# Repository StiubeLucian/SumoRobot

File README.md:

# SumoRobot
Initial Creation of a complete sumo mega firmware with oled screen and multiple settings available.

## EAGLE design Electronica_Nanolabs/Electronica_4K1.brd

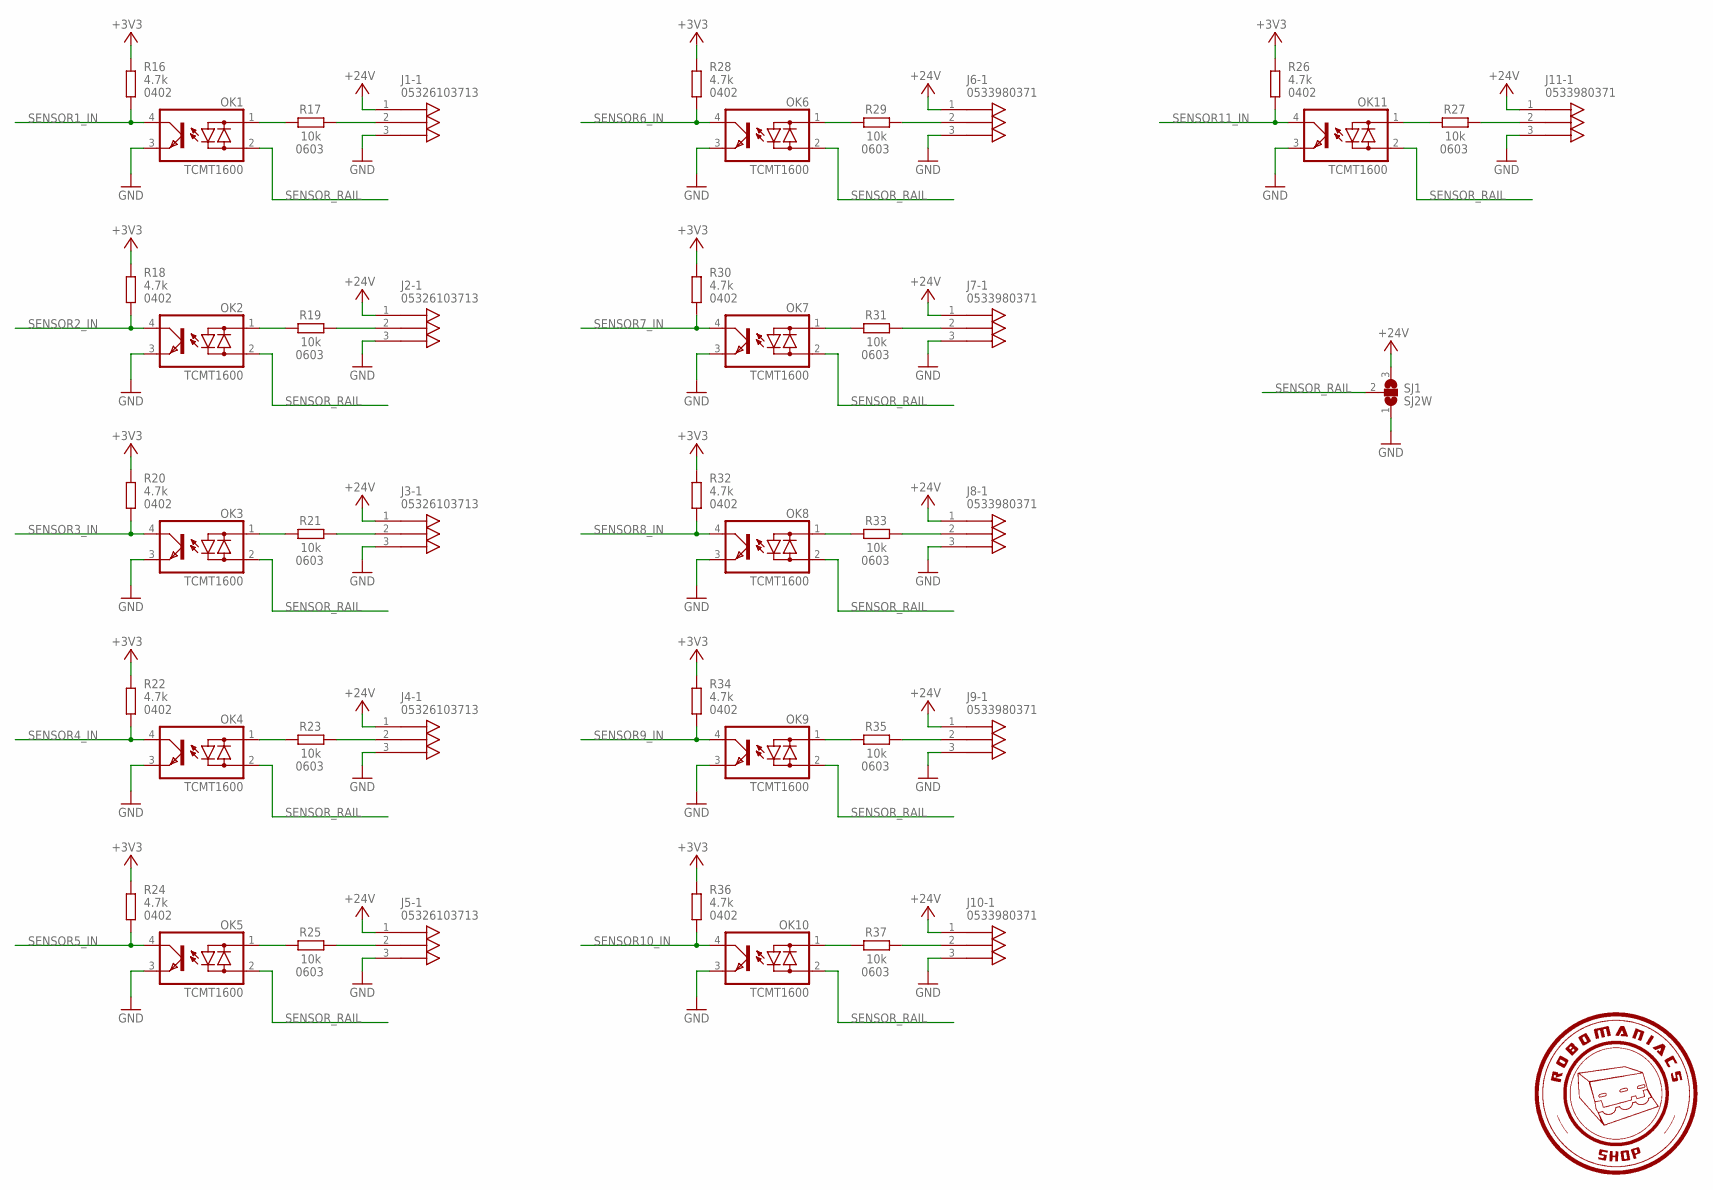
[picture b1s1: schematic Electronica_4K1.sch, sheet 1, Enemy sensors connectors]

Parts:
J1, J2, J3, J4, J5: 05326103713; PICOBLADE53261-0371
J6, J7, J8, J9, J10, J11: 0533980371; PICOBLADE53398-0571
OK1, OK2, OK3, OK4, OK5, OK6, OK7, OK8, OK9, OK10, OK11: TCMT1600; SOP-4
R16, R18, R20, R22, R24, R26, R28, R30, R32, R34, R36: 4.7k; R0402_IPC; MPN AC0402FR-074K7L
R17, R19, R21, R23, R25, R27, R29, R31, R33, R35, R37: 10k; R0603
SJ1: SJ2W; SJ2W_1X1.5_NO

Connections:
+3V3: R16.1, R18.1, R20.1, R22.1, R24.1, R26.1, R28.1, R30.1, R32.1, R34.1, R36.1; also elsewhere on the board
+24V: J1.1, J2.1, J3.1, J4.1, J5.1, J6.1, J7.1, J8.1, J9.1, J10.1, J11.1, SJ1.3; also elsewhere on the board
GND: J1.3, J2.3, J3.3, J4.3, J5.3, J6.3, J7.3, J8.3, J9.3, J10.3, J11.3, OK1.3 (E), OK2.3 (E), OK3.3 (E), OK4.3 (E), OK5.3 (E), OK6.3 (E), OK7.3 (E), OK8.3 (E), OK9.3 (E), OK10.3 (E), OK11.3 (E), SJ1.1; also elsewhere on the board
unnamed: J1.2, R17.2
unnamed: J2.2, R19.2
unnamed: OK1.1 (AC1), R17.1
unnamed: OK2.1 (AC1), R19.1
unnamed: J3.2, R21.2
unnamed: OK3.1 (AC1), R21.1
unnamed: J4.2, R23.2
unnamed: OK4.1 (AC1), R23.1
unnamed: J5.2, R25.2
unnamed: OK5.1 (AC1), R25.1
unnamed: J11.2, R27.2
unnamed: OK11.1 (AC1), R27.1
unnamed: J6.2, R29.2
unnamed: OK6.1 (AC1), R29.1
unnamed: J7.2, R31.2
unnamed: OK7.1 (AC1), R31.1
unnamed: J8.2, R33.2
unnamed: OK8.1 (AC1), R33.1
unnamed: J9.2, R35.2
unnamed: OK9.1 (AC1), R35.1
unnamed: J10.2, R37.2
unnamed: OK10.1 (AC1), R37.1
SENSOR1_IN: OK1.4 (C), R16.2; also elsewhere on the board
SENSOR2_IN: OK2.4 (C), R18.2; also elsewhere on the board
SENSOR3_IN: OK3.4 (C), R20.2; also elsewhere on the board
SENSOR4_IN: OK4.4 (C), R22.2; also elsewhere on the board
SENSOR5_IN: OK5.4 (C), R24.2; also elsewhere on the board
SENSOR6_IN: OK6.4 (C), R28.2; also elsewhere on the board
SENSOR7_IN: OK7.4 (C), R30.2; also elsewhere on the board
SENSOR8_IN: OK8.4 (C), R32.2; also elsewhere on the board
SENSOR9_IN: OK9.4 (C), R34.2; also elsewhere on the board
SENSOR10_IN: OK10.4 (C), R36.2; also elsewhere on the board
SENSOR11_IN: OK11.4 (C), R26.2; also elsewhere on the board
SENSOR_RAIL: OK1.2 (AC2), OK2.2 (AC2), OK3.2 (AC2), OK4.2 (AC2), OK5.2 (AC2), OK6.2 (AC2), OK7.2 (AC2), OK8.2 (AC2), OK9.2 (AC2), OK10.2 (AC2), OK11.2 (AC2), SJ1.2

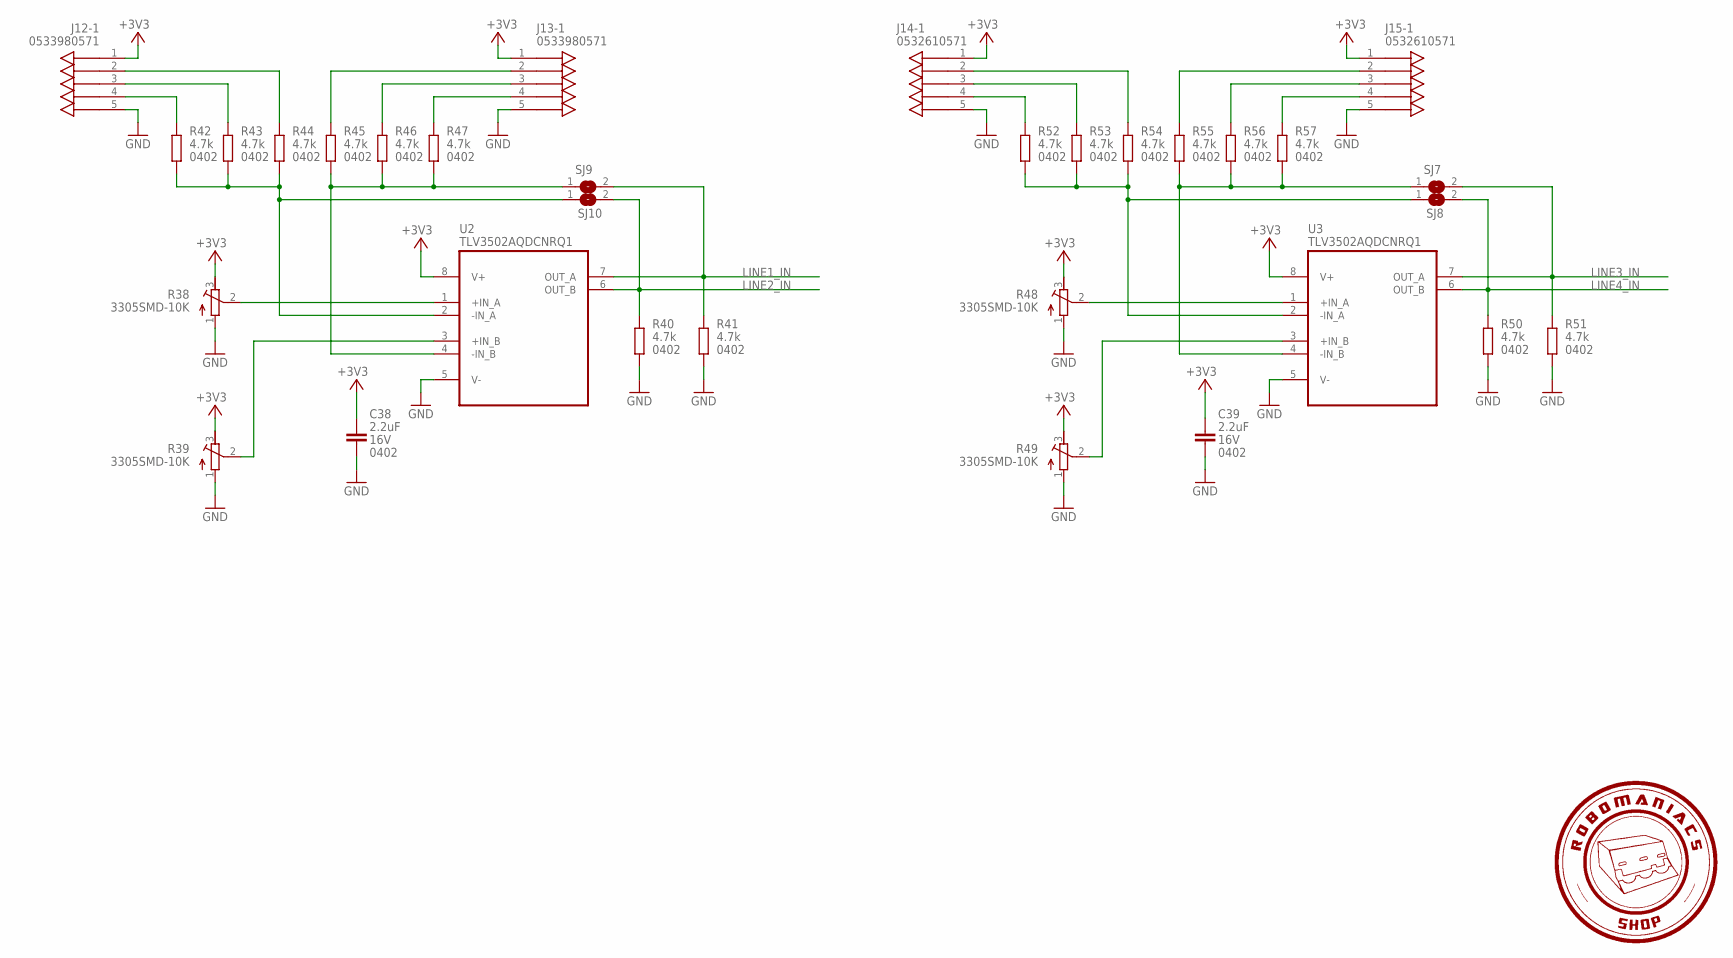
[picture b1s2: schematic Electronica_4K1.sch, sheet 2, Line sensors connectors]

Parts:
C38, C39: 2.2uF; C0402_IPC; VOLTAGE 16V; MPN GRM155R61C225ME15D
J12, J13: 0533980571; PICOBLADE53398-0571
J14, J15: 0532610571; PICOBLADE53261-0571
R38, R39, R48, R49: 3305SMD-10K; RTRIM3103
R40, R41, R42, R43, R44, R45, R46, R47, R50, R51, R52, R53, R54, R55, R56, R57: 4.7k; R0402_IPC; MPN AC0402FR-074K7L
SJ7, SJ8, SJ9, SJ10: SJ_1.5X1_NO; SJ_1X1.5_NO
U2, U3: TLV3502AQDCNRQ1; SOT65P280X145-8N

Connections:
+3V3: C38.1, C39.1, J12.1, J13.1, J14.1, J15.1, R38.3 (E), R39.3 (E), R48.3 (E), R49.3 (E), U2.8 (V+), U3.8 (V+); also elsewhere on the board
GND: C38.2, C39.2, J12.5, J13.5, J14.5, J15.5, R38.1 (A), R39.1 (A), R40.2, R41.2, R48.1 (A), R49.1 (A), R50.2, R51.2, U2.5 (V-), U3.5 (V-); also elsewhere on the board
LINE1_IN: R41.1, SJ9.2, U2.7 (OUT_A); also elsewhere on the board
LINE2_IN: R40.1, SJ10.2, U2.6 (OUT_B); also elsewhere on the board
LINE3_IN: R51.1, SJ7.2, U3.7 (OUT_A); also elsewhere on the board
LINE4_IN: R50.1, SJ8.2, U3.6 (OUT_B); also elsewhere on the board
unnamed: R38.2 (S), U2.1 (+IN_A)
unnamed: R39.2 (S), U2.3 (+IN_B)
unnamed: R42.2, R43.2, R44.2, SJ10.1, U2.2 (-IN_A)
unnamed: R45.2, R46.2, R47.2, SJ9.1, U2.4 (-IN_B)
unnamed: J13.4, R47.1
unnamed: J13.3, R46.1
unnamed: J12.4, R42.1
unnamed: J12.3, R43.1
unnamed: J12.2, R44.1
unnamed: J13.2, R45.1
unnamed: R48.2 (S), U3.1 (+IN_A)
unnamed: R49.2 (S), U3.3 (+IN_B)
unnamed: R52.2, R53.2, R54.2, SJ8.1, U3.2 (-IN_A)
unnamed: R55.2, R56.2, R57.2, SJ7.1, U3.4 (-IN_B)
unnamed: J14.4, R52.1
unnamed: J14.3, R53.1
unnamed: J14.2, R54.1
unnamed: J15.4, R57.1
unnamed: J15.3, R56.1
unnamed: J15.2, R55.1

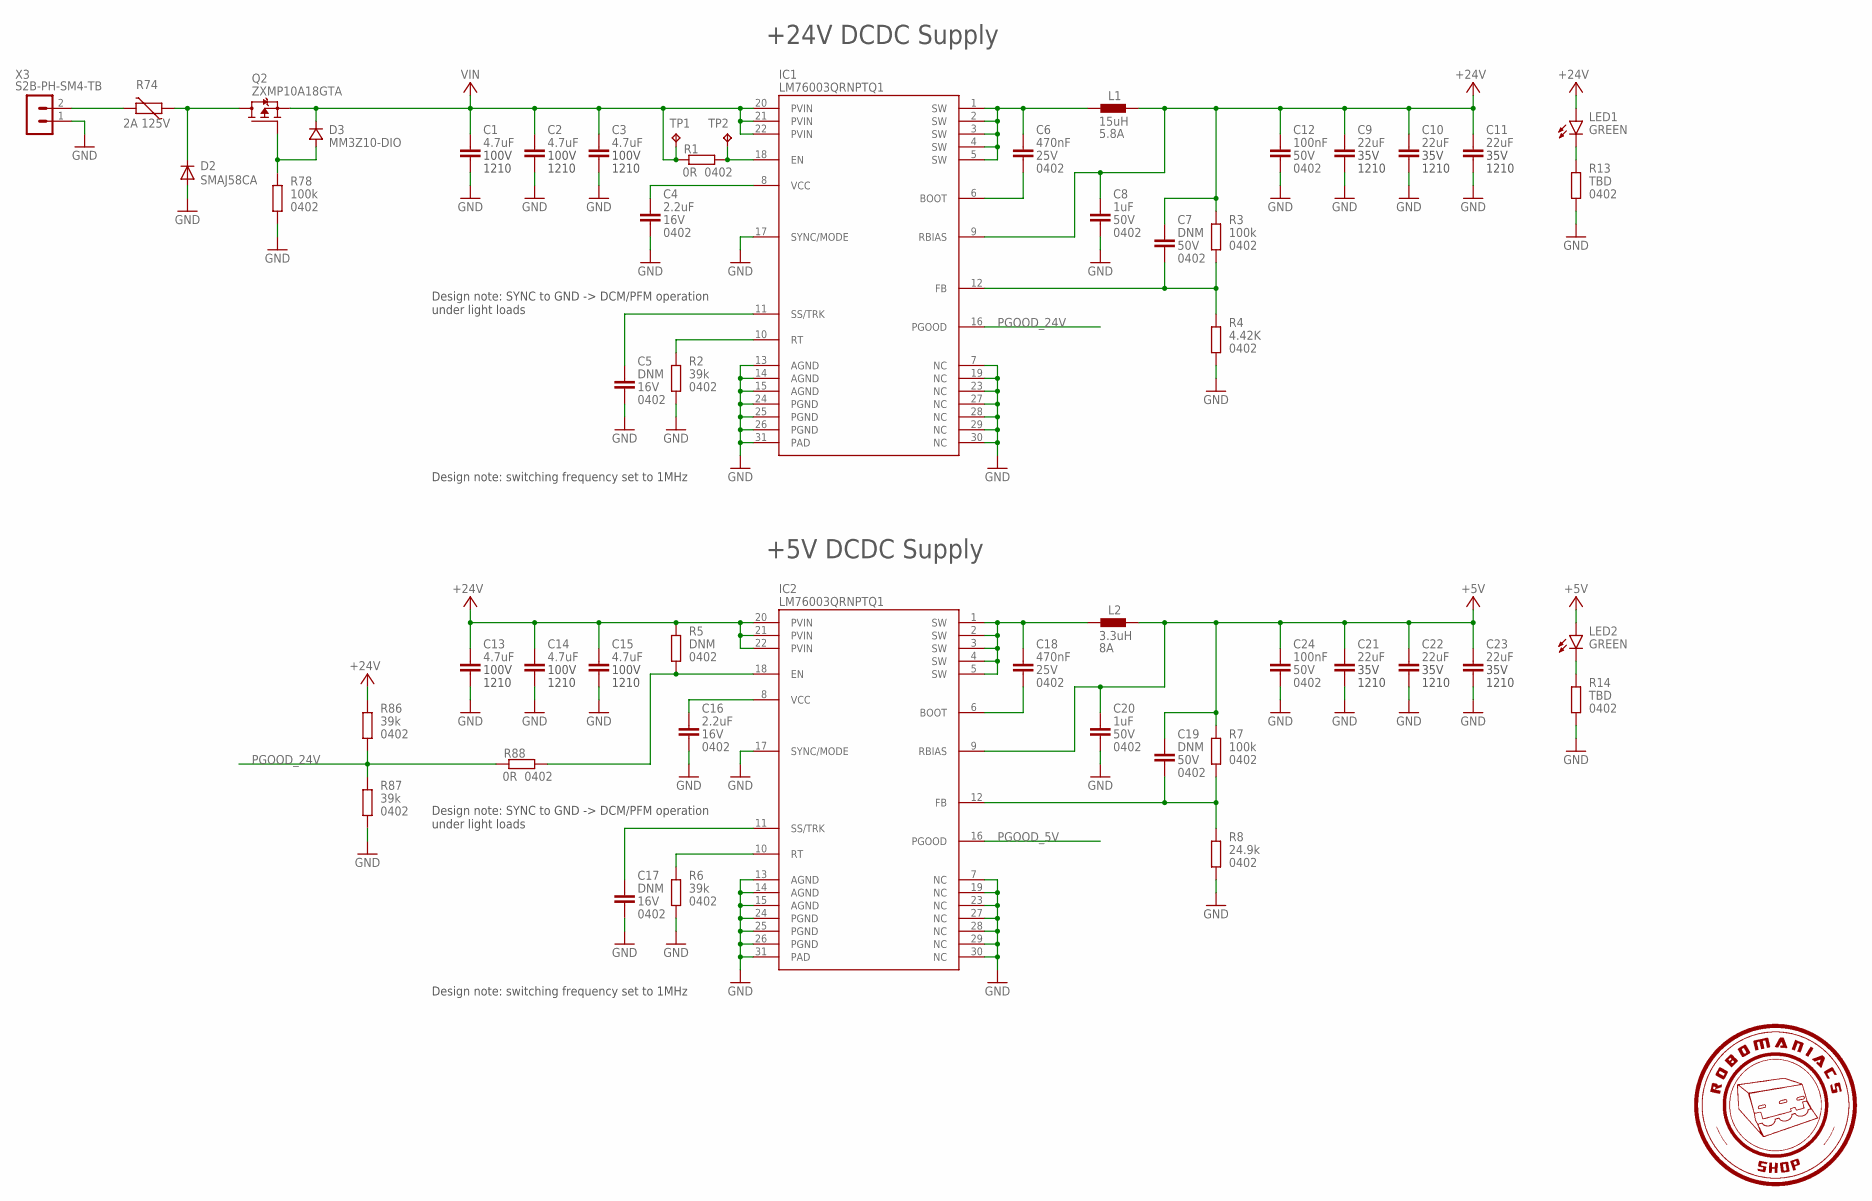
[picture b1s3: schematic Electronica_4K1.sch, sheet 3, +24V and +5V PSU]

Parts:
C1, C2, C3, C13, C14, C15: 4.7uF; C1210; VOLTAGE 100V; MPN CL32B475KCVZ3WE
C4, C16: 2.2uF; C0402_IPC; VOLTAGE 16V; MPN GRM155R61C225ME15D
C5, C17: DNM; C0402_IPC; VOLTAGE 16V; MPN GRM155R61C225ME15D
C6, C18: 470nF; C0402_IPC; VOLTAGE 25V; MPN GRM155R61E474KE01D
C7, C19: DNM; C0402_IPC; VOLTAGE 50V; MPN GRM155R61E474KE01D
C8, C20: 1uF; C0402_IPC; VOLTAGE 50V; MPN GRM155R61H105ME05D
C9, C10, C11, C21, C22, C23: 22uF; C1210; VOLTAGE 35V; MPN GMK325BJ226MM-P
C12, C24: 100nF; C0402_IPC; VOLTAGE 50V; MPN GRM155R71H104ME14D
D2: SMAJ58CA; SMA
D3: MM3Z10-DIO; SOD323
IC1, IC2: LM76003QRNPTQ1; WQFN30_6X4MM
L1: 15uH; XAL6060; MPN XAL6060-153MEC
L2: 3.3uH; XAL6060; MPN XAL6030-332MEC
LED1, LED2: GREEN; CHIPLED_0603
Q2: ZXMP10A18GTA; SOT223
R1, R88: 0R; R0402_IPC; MPN RC0402JR-130RL
R2, R6, R86, R87: 39k; R0402_IPC; MPN AC0402FR-0739KL
R3, R7, R78: 100k; R0402_IPC; MPN AC0402FR-07100KL
R4: 4.42K; R0402_IPC; MPN RT0402DRE074K42L
R5: DNM; R0402_IPC; MPN RC0402JR-130RL
R8: 24.9k; R0402_IPC; MPN RT0402FRE0724K9L
R13, R14: TBD; R0402_IPC; MPN RT0402DRE074K42L
R74: 2A 125V; CT/CN1206
TP1, TP2: TPTP20SQ; TP20SQ
X3: S2B-PH-SM4-TB

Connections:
+5V: C19.1, C20.1, C21.1, C22.1, C23.1, C24.1, IC2.9 (RBIAS), L2.2, LED2.A, R7.2; also elsewhere on the board
+24V: C7.1, C8.1, C9.1, C10.1, C11.1, C12.1, C13.1, C14.1, C15.1, IC1.9 (RBIAS), IC2.20 (PVIN), IC2.21 (PVIN), IC2.22 (PVIN), L1.2, LED1.A, R3.2, R5.1, R86.2; also elsewhere on the board
GND: C1.2, C2.2, C3.2, C4.2, C5.2, C8.2, C9.2, C10.2, C11.2, C12.2, C13.2, C14.2, C15.2, C16.2, C17.2, C20.2, C21.2, C22.2, C23.2, C24.2, D2.A, IC1.7 (NC), IC1.13 (AGND), IC1.14 (AGND), IC1.15 (AGND), IC1.17 (SYNC/MODE), IC1.19 (NC), IC1.23 (NC), IC1.24 (PGND), IC1.25 (PGND), IC1.26 (PGND), IC1.27 (NC), IC1.28 (NC), IC1.29 (NC), IC1.30 (NC), IC1.31 (PAD), IC2.7 (NC), IC2.13 (AGND), IC2.14 (AGND), IC2.15 (AGND), IC2.17 (SYNC/MODE), IC2.19 (NC), IC2.23 (NC), IC2.24 (PGND), IC2.25 (PGND), IC2.26 (PGND), IC2.27 (NC), IC2.28 (NC), IC2.29 (NC), IC2.30 (NC), IC2.31 (PAD), R2.1, R4.1, R6.1, R8.1, R13.1, R14.1, R78.1, R87.1, X3.1; also elsewhere on the board
unnamed: C4.1, IC1.8 (VCC)
unnamed: IC1.18 (EN), R1.2, TP2.TP
unnamed: IC1.10 (RT), R2.2
unnamed: C7.2, IC1.12 (FB), R3.1, R4.2
unnamed: C5.1, IC1.11 (SS/TRK)
unnamed: C16.1, IC2.8 (VCC)
unnamed: C6.1, IC1.1 (SW), IC1.2 (SW), IC1.3 (SW), IC1.4 (SW), IC1.5 (SW), L1.1
unnamed: C6.2, IC1.6 (BOOT)
unnamed: C17.1, IC2.11 (SS/TRK)
unnamed: IC2.10 (RT), R6.2
unnamed: C18.1, IC2.1 (SW), IC2.2 (SW), IC2.3 (SW), IC2.4 (SW), IC2.5 (SW), L2.1
unnamed: C18.2, IC2.6 (BOOT)
unnamed: C19.2, IC2.12 (FB), R7.1, R8.2
unnamed: LED1.C, R13.2
unnamed: LED2.C, R14.2
unnamed: D3.2 (A), Q2.1 (G), R78.2
unnamed: D2.C, Q2.2 (D), Q2.4 (D), R74.1
unnamed: R74.2, X3.2
unnamed: IC2.18 (EN), R5.2, R88.2
PGOOD_5V: IC2.16 (PGOOD)
PGOOD_24V: IC1.16 (PGOOD), R86.1, R87.2, R88.1; also elsewhere on the board
VIN: C1.1, C2.1, C3.1, D3.1 (C), IC1.20 (PVIN), IC1.21 (PVIN), IC1.22 (PVIN), Q2.3 (S), R1.1, TP1.TP

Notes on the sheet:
Design note: switching frequency set to 1MHz
Design note: SYNC to GND -> DCM/PFM operation under light loads
+24V DCDC Supply
+5V DCDC Supply

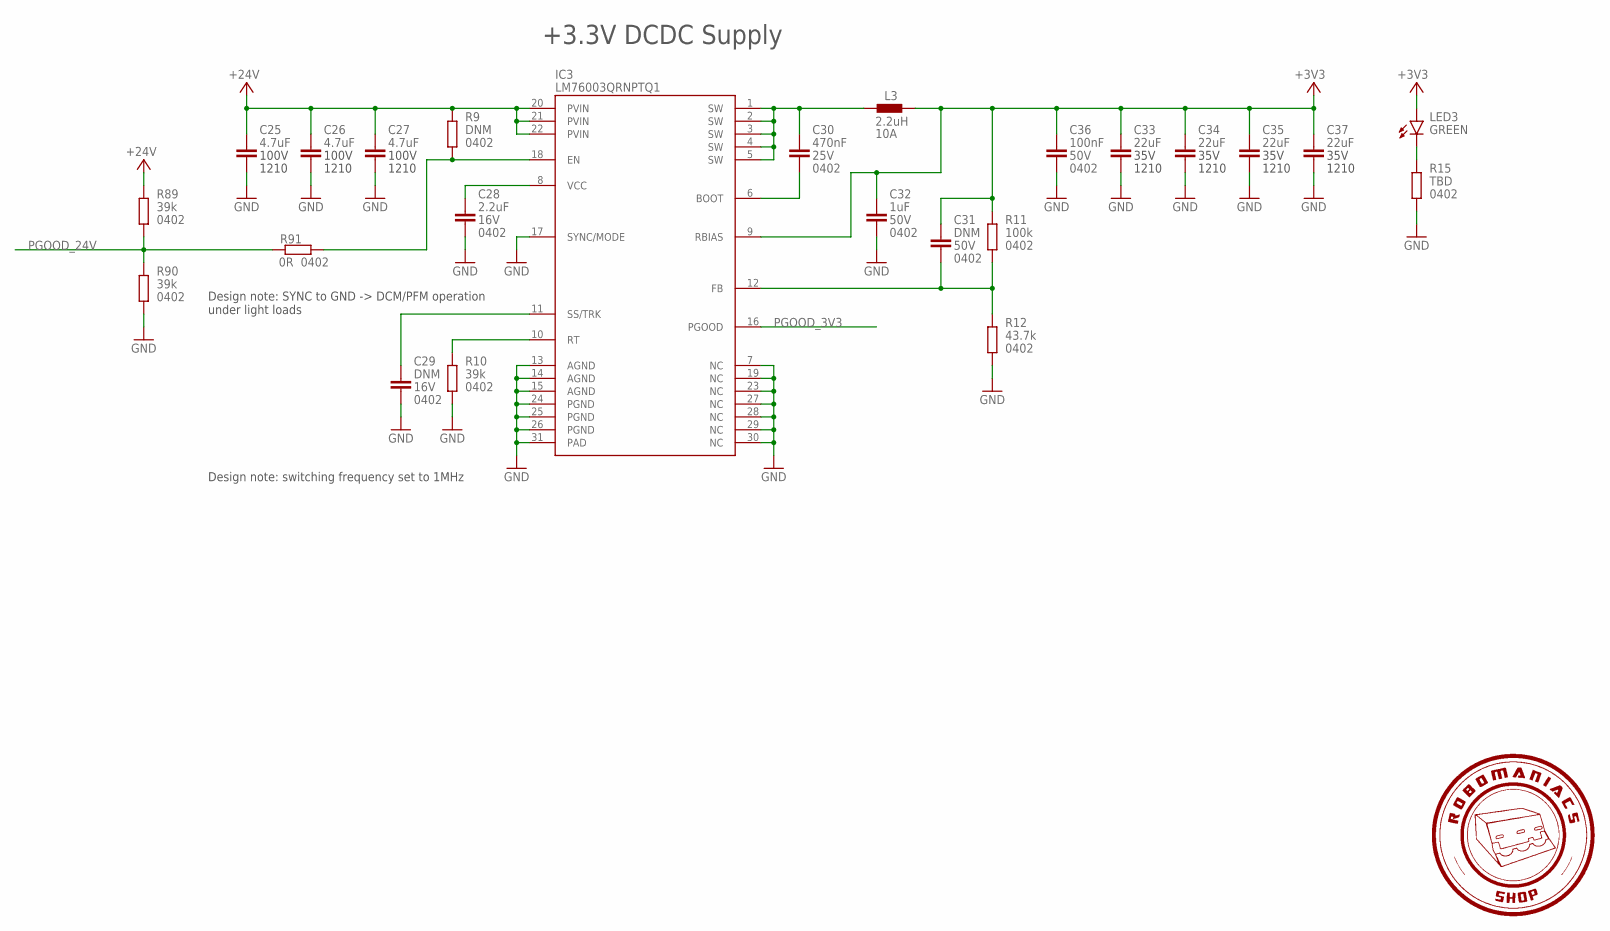
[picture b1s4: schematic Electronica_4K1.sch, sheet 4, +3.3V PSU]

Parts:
C25, C26, C27: 4.7uF; C1210; VOLTAGE 100V; MPN CL32B475KCVZ3WE
C28: 2.2uF; C0402_IPC; VOLTAGE 16V; MPN GRM155R61C225ME15D
C29: DNM; C0402_IPC; VOLTAGE 16V; MPN GRM155R61C225ME15D
C30: 470nF; C0402_IPC; VOLTAGE 25V; MPN GRM155R61E474KE01D
C31: DNM; C0402_IPC; VOLTAGE 50V; MPN GRM155R61E474KE01D
C32: 1uF; C0402_IPC; VOLTAGE 50V; MPN GRM155R61H105ME05D
C33, C34, C35, C37: 22uF; C1210; VOLTAGE 35V; MPN GMK325BJ226MM-P
C36: 100nF; C0402_IPC; VOLTAGE 50V; MPN GRM155R71H104ME14D
IC3: LM76003QRNPTQ1; WQFN30_6X4MM
L3: 2.2uH; XAL6060; MPN XAL6030-222MEC
LED3: GREEN; CHIPLED_0603
R9: DNM; R0402_IPC; MPN RC0402JR-130RL
R10, R89, R90: 39k; R0402_IPC; MPN AC0402FR-0739KL
R11: 100k; R0402_IPC; MPN AC0402FR-07100KL
R12: 43.7k; R0402_IPC; MPN TNPW040243K7BEED
R15: TBD; R0402_IPC; MPN RT0402DRE074K42L
R91: 0R; R0402_IPC; MPN RC0402JR-130RL

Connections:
+3V3: C31.1, C32.1, C33.1, C34.1, C35.1, C36.1, C37.1, IC3.9 (RBIAS), L3.2, LED3.A, R11.2; also elsewhere on the board
+24V: C25.1, C26.1, C27.1, IC3.20 (PVIN), IC3.21 (PVIN), IC3.22 (PVIN), R9.1, R89.2; also elsewhere on the board
GND: C25.2, C26.2, C27.2, C28.2, C29.2, C32.2, C33.2, C34.2, C35.2, C36.2, C37.2, IC3.7 (NC), IC3.13 (AGND), IC3.14 (AGND), IC3.15 (AGND), IC3.17 (SYNC/MODE), IC3.19 (NC), IC3.23 (NC), IC3.24 (PGND), IC3.25 (PGND), IC3.26 (PGND), IC3.27 (NC), IC3.28 (NC), IC3.29 (NC), IC3.30 (NC), IC3.31 (PAD), R10.1, R12.1, R15.1, R90.1; also elsewhere on the board
unnamed: IC3.18 (EN), R9.2, R91.2
unnamed: C28.1, IC3.8 (VCC)
unnamed: C29.1, IC3.11 (SS/TRK)
unnamed: IC3.10 (RT), R10.2
unnamed: C30.1, IC3.1 (SW), IC3.2 (SW), IC3.3 (SW), IC3.4 (SW), IC3.5 (SW), L3.1
unnamed: C30.2, IC3.6 (BOOT)
unnamed: C31.2, IC3.12 (FB), R11.1, R12.2
unnamed: LED3.C, R15.2
PGOOD_3V3: IC3.16 (PGOOD)
PGOOD_24V: R89.1, R90.2, R91.1; also elsewhere on the board

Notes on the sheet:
Design note: switching frequency set to 1MHz
Design note: SYNC to GND -> DCM/PFM operation under light loads
+3.3V DCDC Supply

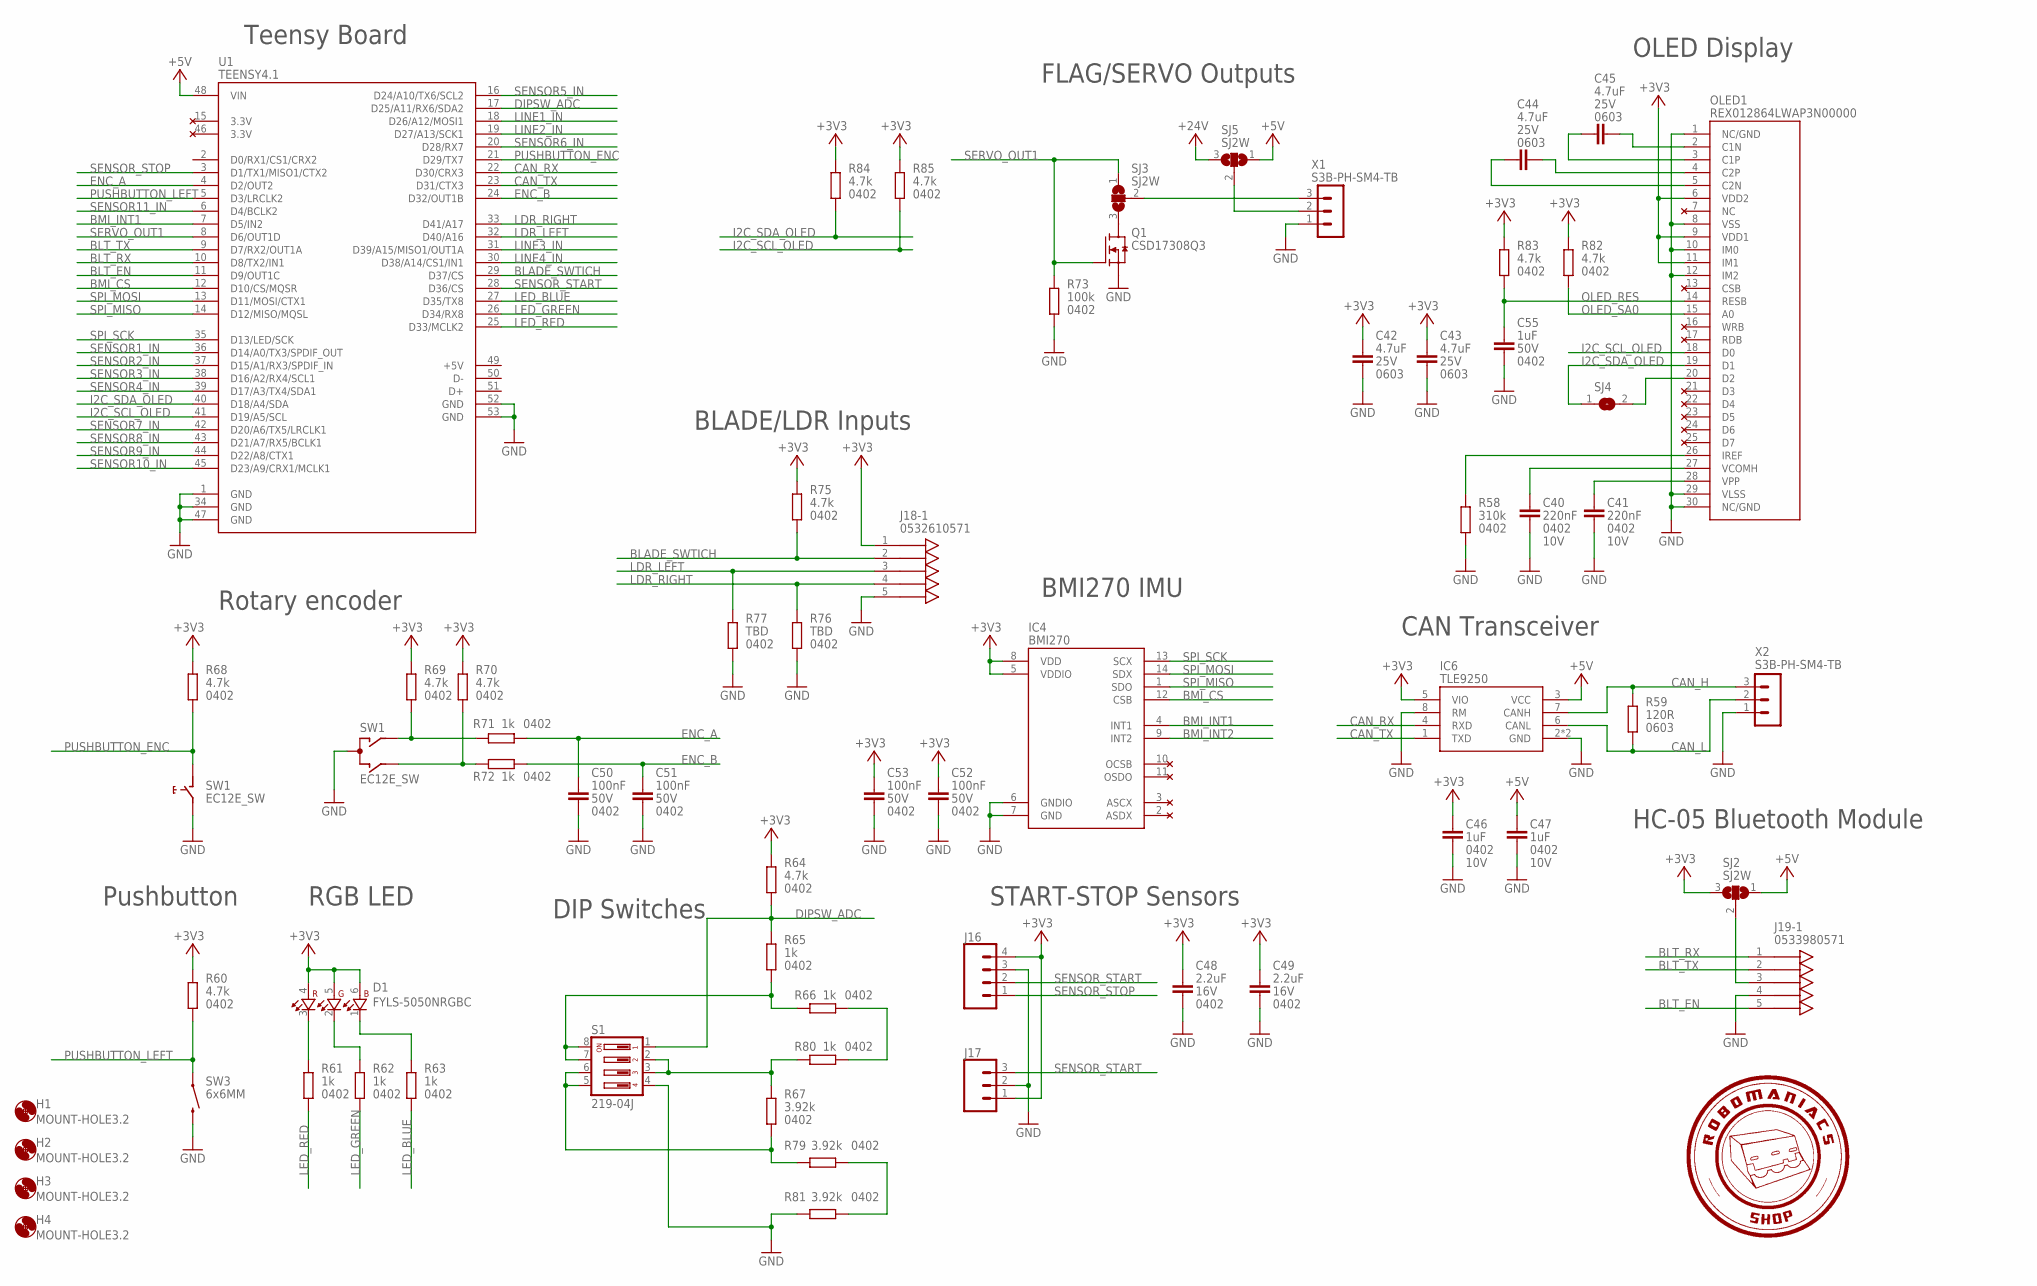
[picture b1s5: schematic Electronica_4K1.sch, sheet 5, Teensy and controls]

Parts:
C40, C41: 220nF; C0402_IPC; VOLTAGE 10V
C42, C43, C44, C45: 4.7uF; C0603; VOLTAGE 25V
C46, C47: 1uF; C0402_IPC; VOLTAGE 10V
C48, C49: 2.2uF; C0402_IPC; VOLTAGE 16V; MPN GRM155R61C225ME15D
C50, C51, C52, C53: 100nF; C0402_IPC; VOLTAGE 50V; MPN GRM155R71H104ME14D
C55: 1uF; C0402_IPC; VOLTAGE 50V; MPN GRM155R61H105ME05D
D1: FYLS-5050NRGBC
H1, H2, H3, H4: MOUNT-HOLE3.2; 3,2
IC4: BMI270; LGA_BMI270
IC6: TLE9250; PG-TSON-8
J16: CONN_04; 1X04
J17: CONN_03; 1X03
J18: 0532610571; PICOBLADE53261-0571
J19: 0533980571; PICOBLADE53398-0571
OLED1: REX012864LWAP3N00000
Q1: CSD17308Q3; VSON-3X3
R58: 310k; R0402_IPC
R59: 120R; R0603
R60, R64, R68, R69, R70, R75, R82, R83, R84, R85: 4.7k; R0402_IPC; MPN AC0402FR-074K7L
R61, R62, R63, R65, R66, R71, R72, R80: 1k; R0402_IPC; MPN AC0402FR-071KL
R67, R79, R81: 3.92k; R0402_IPC; MPN AC0402FR-073K92L
R73: 100k; R0402_IPC; MPN AC0402FR-07100KL
R76, R77: TBD; R0402_IPC; MPN RT0402DRE074K42L
S1: 219-04J; CTS-219-04J
SJ2, SJ3, SJ5: SJ2W; SJ2W_1X1.5_NO
SJ4: SJ_1.5X1_NO; SJ_1X1.5_NO
SW1: EC12E_SW; ALPS_EC12E_SW
SW3: 6x6MM; TACTILE_SWITCH_SMD_6.2MM_TALL; MPN TACTM-613N-F
U1: TEENSY4.1
X1, X2: S3B-PH-SM4-TB

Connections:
+3V3: C42.1, C43.1, C46.1, C48.1, C49.1, C52.1, C53.1, D1.4 (RED_A), D1.5 (GREEN_A), D1.6 (BLUE_A), IC4.5 (VDDIO), IC4.8 (VDD), IC6.5 (VIO), J16.4, J17.1, J18.1, OLED1.6 (VDD2), OLED1.9 (VDD1), OLED1.11 (IM1), R60.1, R64.1, R68.1, R69.1, R70.1, R75.1, R82.1, R83.1, R84.1, R85.1, SJ2.3; also elsewhere on the board
+5V: C47.1, IC6.3 (VCC), SJ2.1, SJ5.1, U1.48 (VIN); also elsewhere on the board
+24V: SJ5.3; also elsewhere on the board
BLADE_SWTICH: J18.2, R75.2, U1.29 (D37/CS)
BLT_EN: J19.5, U1.11 (D9/OUT1C)
BLT_RX: J19.1, U1.10 (D8/TX2/IN1)
BLT_TX: J19.2, U1.9 (D7/RX2/OUT1A)
BMI_CS: IC4.12 (CSB), U1.12 (D10/CS/MQSR)
BMI_INT1: IC4.4 (INT1), U1.7 (D5/IN2)
BMI_INT2: IC4.9 (INT2)
CAN_H: IC6.7 (CANH), R59.2, X2.3
CAN_L: IC6.6 (CANL), R59.1, X2.2
CAN_RX: IC6.4 (RXD), U1.22 (D30/CRX3)
CAN_TX: IC6.1 (TXD), U1.23 (D31/CTX3)
DIPSW_ADC: R64.2, R65.1, S1.1, U1.17 (D25/A11/RX6/SDA2)
ENC_A: C50.1, R71.1, U1.4 (D2/OUT2)
ENC_B: C51.1, R72.1, U1.24 (D32/OUT1B)
GND: C40.2, C41.2, C42.2, C43.2, C46.2, C47.2, C48.2, C49.2, C50.2, C51.2, C52.2, C53.2, C55.2, IC4.6 (GNDIO), IC4.7 (GND), IC6.2 (GND), IC6.8 (RM), IC6.EP (GND), J16.3, J17.2, J18.5, J19.4, OLED1.1 (NC/GND), OLED1.8 (VSS), OLED1.10 (IM0), OLED1.12 (IM2), OLED1.29 (VLSS), OLED1.30 (NC/GND), Q1.1 (S), Q1.2 (S), Q1.3 (S), R58.1, R73.1, R76.1, R77.1, R81.1, S1.4, SW1.C, SW1.E (2), SW3.B2 (2), U1.1 (GND), U1.34 (GND), U1.47 (GND), U1.52 (GND), U1.53 (GND), X1.1, X2.1; also elsewhere on the board
I2C_SCL_OLED: OLED1.18 (D0), R85.2, U1.41 (D19/A5/SCL)
I2C_SDA_OLED: OLED1.19 (D1), R84.2, SJ4.1, U1.40 (D18/A4/SDA)
LDR_LEFT: J18.3, R77.2, U1.32 (D40/A16)
LDR_RIGHT: J18.4, R76.2, U1.33 (D41/A17)
LED_BLUE: R63.1, U1.27 (D35/TX8)
LED_GREEN: R62.1, U1.26 (D34/RX8)
LED_RED: R61.1, U1.25 (D33/MCLK2)
LINE1_IN: U1.18 (D26/A12/MOSI1); also elsewhere on the board
LINE2_IN: U1.19 (D27/A13/SCK1); also elsewhere on the board
LINE3_IN: U1.31 (D39/A15/MISO1/OUT1A); also elsewhere on the board
LINE4_IN: U1.30 (D38/A14/CS1/IN1); also elsewhere on the board
unnamed: C45.2, OLED1.2 (C1N)
unnamed: C45.1, OLED1.3 (C1P)
unnamed: C44.2, OLED1.4 (C2P)
unnamed: C44.1, OLED1.5 (C2N)
unnamed: OLED1.26 (IREF), R58.2
unnamed: C40.1, OLED1.27 (VCOMH)
unnamed: C41.1, OLED1.28 (VPP)
unnamed: D1.3 (RED_K), R61.2
unnamed: D1.2 (GREEN_K), R62.2
unnamed: D1.1 (BLUE_K), R63.2
unnamed: R69.2, R71.2, SW1.A
unnamed: R70.2, R72.2, SW1.B
unnamed: J19.3, SJ2.2
unnamed: SJ5.2, X1.2
unnamed: SJ3.2, X1.3
unnamed: Q1.5 (D), Q1.6 (D), Q1.7 (D), Q1.8 (D), SJ3.3
unnamed: R65.2, R66.2, S1.7, S1.8
unnamed: R79.2, R81.2
unnamed: R66.1, R80.1
unnamed: OLED1.20 (D2), SJ4.2
unnamed: R67.1, R80.2, S1.2, S1.3
unnamed: R67.2, R79.1, S1.5, S1.6
OLED_RES: C55.1, OLED1.14 (RESB), R83.2
OLED_SA0: OLED1.15 (A0), R82.2
PUSHBUTTON_ENC: R68.2, SW1.D (1), U1.21 (D29/TX7)
PUSHBUTTON_LEFT: R60.2, SW3.A2 (1), U1.5 (D3/LRCLK2)
SENSOR1_IN: U1.36 (D14/A0/TX3/SPDIF_OUT); also elsewhere on the board
SENSOR2_IN: U1.37 (D15/A1/RX3/SPDIF_IN); also elsewhere on the board
SENSOR3_IN: U1.38 (D16/A2/RX4/SCL1); also elsewhere on the board
SENSOR4_IN: U1.39 (D17/A3/TX4/SDA1); also elsewhere on the board
SENSOR5_IN: U1.16 (D24/A10/TX6/SCL2); also elsewhere on the board
SENSOR6_IN: U1.20 (D28/RX7); also elsewhere on the board
SENSOR7_IN: U1.42 (D20/A6/TX5/LRCLK1); also elsewhere on the board
SENSOR8_IN: U1.43 (D21/A7/RX5/BCLK1); also elsewhere on the board
SENSOR9_IN: U1.44 (D22/A8/CTX1); also elsewhere on the board
SENSOR10_IN: U1.45 (D23/A9/CRX1/MCLK1); also elsewhere on the board
SENSOR11_IN: U1.6 (D4/BCLK2); also elsewhere on the board
SENSOR_START: J16.2, J17.3, U1.28 (D36/CS)
SENSOR_STOP: J16.1, U1.3 (D1/TX1/MISO1/CTX2)
SERVO_OUT1: Q1.4 (G), R73.2, SJ3.1, U1.8 (D6/OUT1D)
SPI_MISO: IC4.1 (SDO), U1.14 (D12/MISO/MQSL)
SPI_MOSI: IC4.14 (SDX), U1.13 (D11/MOSI/CTX1)
SPI_SCK: IC4.13 (SCX), U1.35 (D13/LED/SCK)

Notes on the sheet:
HC-05 Bluetooth Module
OLED Display
CAN Transceiver
BMI270 IMU
START-STOP Sensors
DIP Switches
Rotary encoder
RGB LED
Pushbutton
FLAG/SERVO Outputs
Teensy Board
BLADE/LDR Inputs

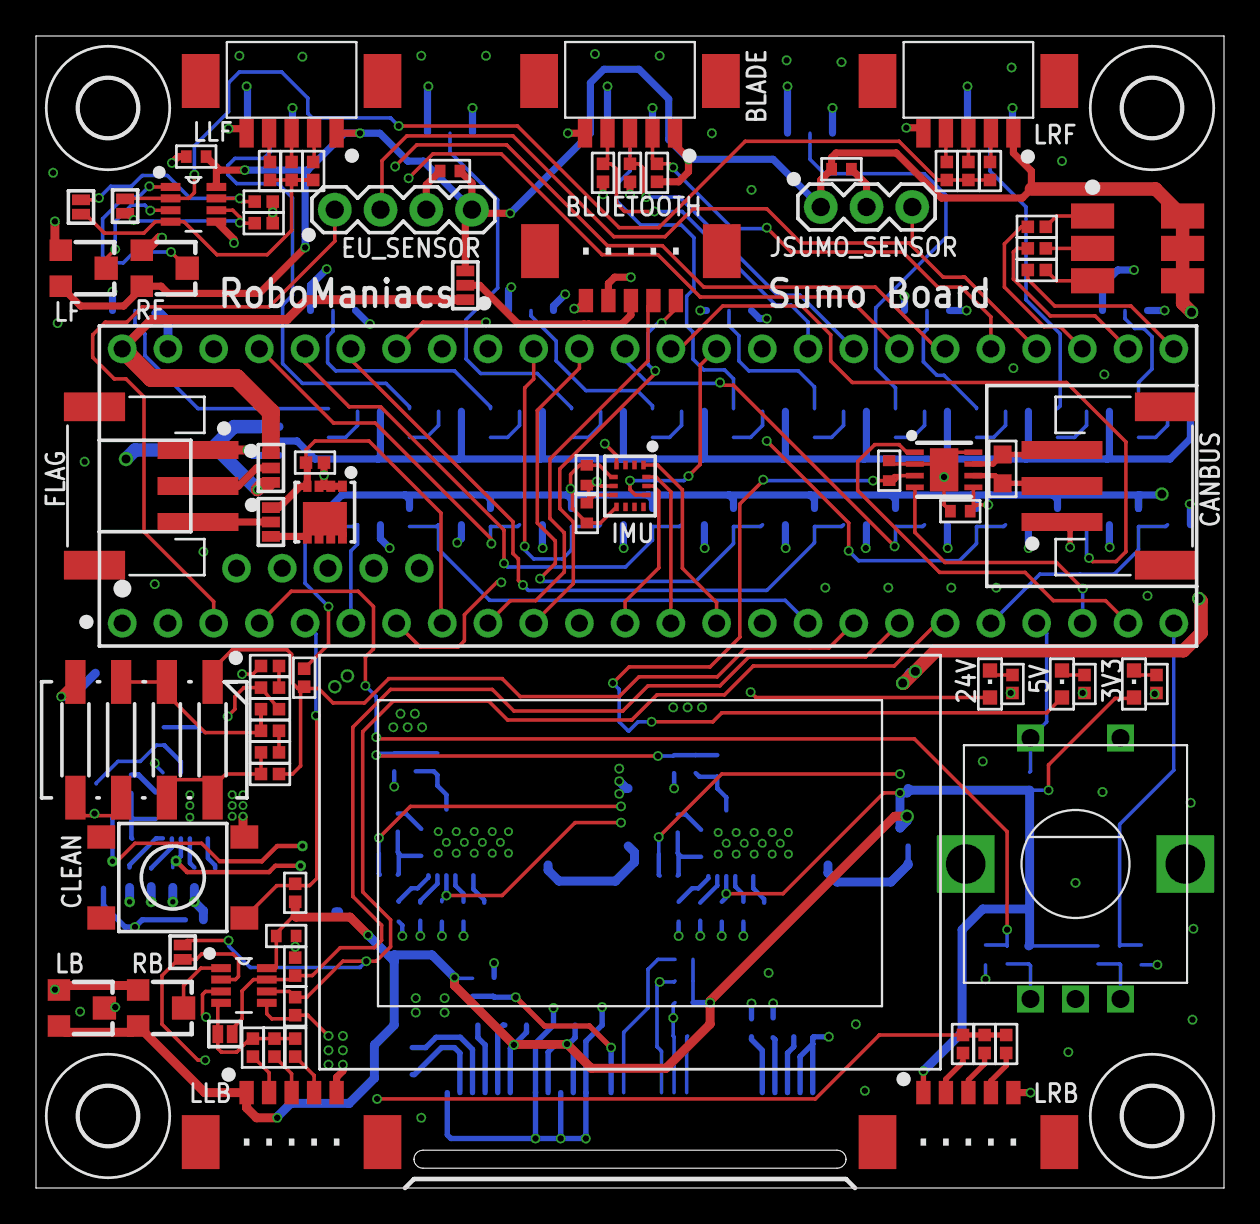
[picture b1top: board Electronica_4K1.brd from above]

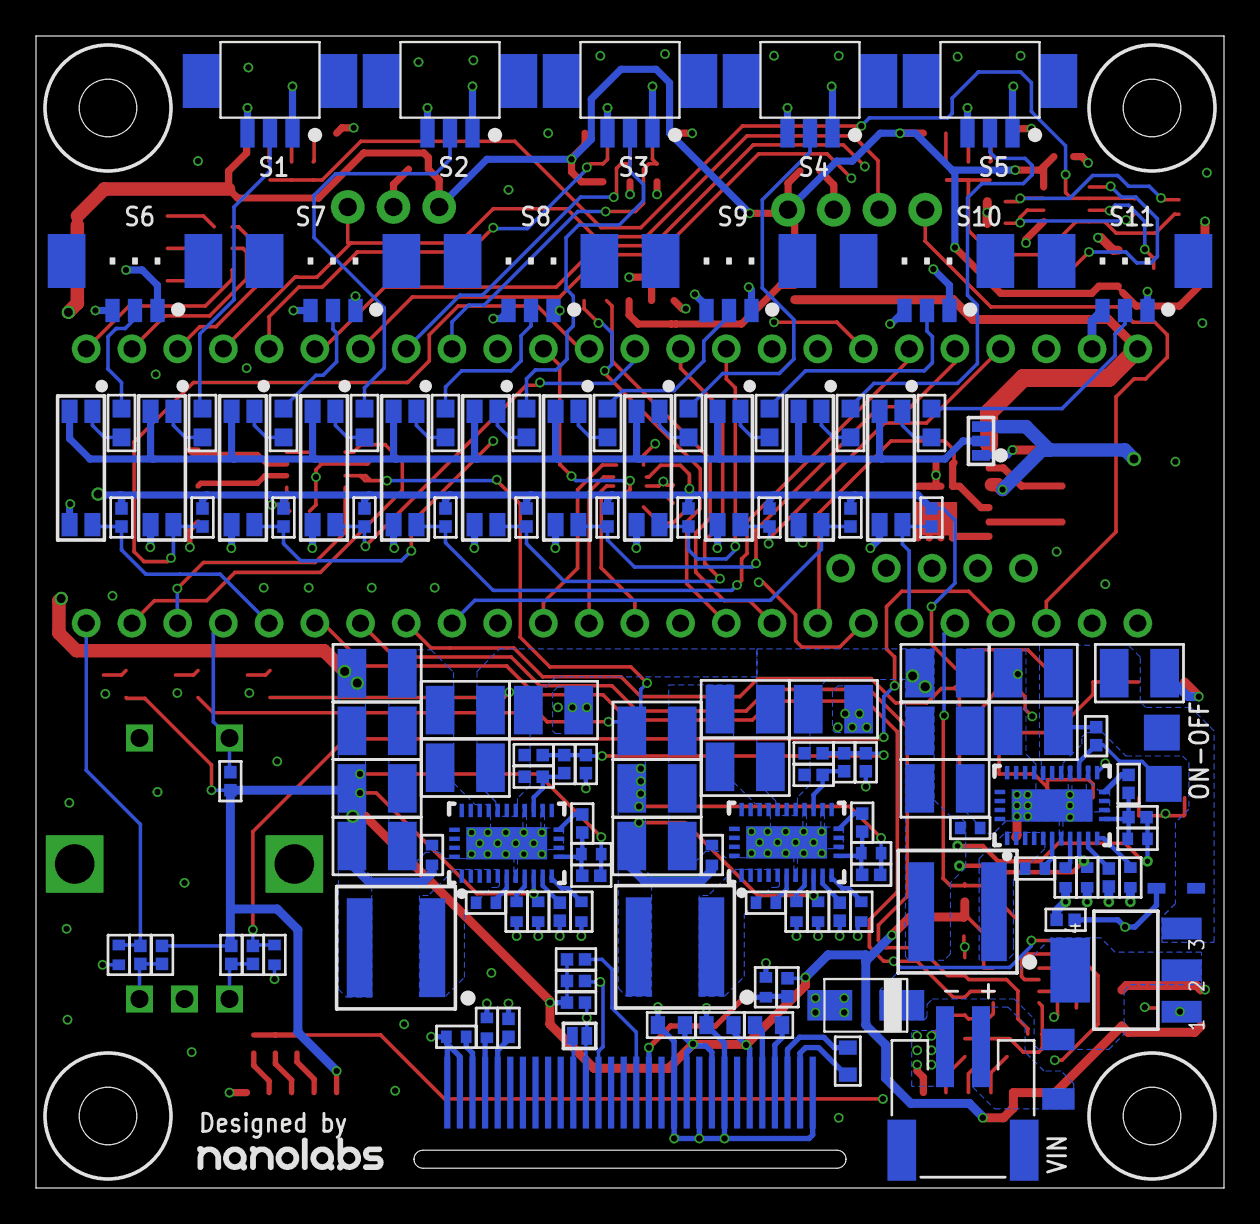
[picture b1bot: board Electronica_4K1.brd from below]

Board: 4 copper layers, 66.0 x 64.0 mm, 217 parts (135 on the bottom side), 143 nets.

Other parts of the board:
U$1: NANOLABS10

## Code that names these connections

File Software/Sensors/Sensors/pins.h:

#ifndef PINS_H
#define PINS_H

// Opponent Sensors
#define Sensor1_in  14
#define Sensor2_in  15
#define Sensor3_in  16
#define Sensor4_in  17
#define Sensor5_in  24
#define Sensor6_in  28
#define Sensor7_in  20
#define Sensor8_in  21
#define Sensor9_in  22
#define Sensor10_in 23
#define Sensor11_in 4

// Line Sensors (Front Corners and Back Corners)
#define LineSensor_FrontLeft  26
#define LineSensor_FrontRight 27
#define LineSensor_BackLeft   39
#define LineSensor_BackRight  38

// Clean Button Pin
const int cleanButtonPin = 3; // Button for cleaning wheels (active-low)

// Rotary Encoder Pins
const int clkPin = 2;  // Rotary encoder CLK pin
const int dtPin = 32;  // Rotary encoder DT pin
const int swPin = 29;  // Rotary encoder button pin

// Function to initialize pins
void initializePins();

#endif // PINS_H

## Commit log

2025-01-07 Add files via upload
    initial files with separated functionalities
2025-01-07 Create FragmentatedCode
2025-01-07 Initial add
    Fragmentated code
2025-01-19 second commit of sw directory
2025-01-19 making menus_@ available
2025-01-19 making menu available
2025-01-19 Restore deleted files and resolve merge conflicts
2025-01-19 Upload files to Firmware folder
2025-01-19 Stable Version of menu with settings - no epprom
2025-01-20 Stable Version of menu with settings - WITH epprom

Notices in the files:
parts and their libraries:
volks73-Molex: Creative Commons Attribution-ShareAlike 3.0 Unported (CC BY-SA 3.0), http://creativecommons.org/licenses/by-sa/3.0/.
SparkFun-Connectors: Licensing: Creative Commons ShareAlike 4.0 International - https://creativecommons.org/licenses/by-sa/4.0
